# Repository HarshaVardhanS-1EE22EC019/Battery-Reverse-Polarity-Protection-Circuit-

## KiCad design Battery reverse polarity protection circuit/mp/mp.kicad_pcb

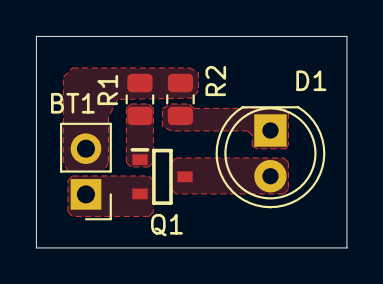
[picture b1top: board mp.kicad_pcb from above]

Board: 2 copper layers, 17.2 x 11.8 mm, 5 parts (0 on the bottom side), 5 nets, no tracks yet.

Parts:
BT1: 9V; PinHeader_1x02_P2.54mm_Vertical
D1: LED; LED_D5.0mm
Q1: PJA3415A-AU_R1_000A1
R1: 100K; R_0805_2012Metric
R2: 1K; R_0805_2012Metric

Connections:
GNDREF: BT1.2 (-), R1.2, R2.1
unnamed: BT1.1 (+), Q1.2 (S)
unnamed: D1.2 (A), Q1.3 (D)
unnamed: D1.1 (K), R2.2
unnamed: Q1.1 (G), R1.1
